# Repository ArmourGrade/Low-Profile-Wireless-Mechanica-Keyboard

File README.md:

# Low-Profile-Wireless-Mechanica-Keyboard
Wireless Mechanical Keyboard featuring the Nice Nano dev board

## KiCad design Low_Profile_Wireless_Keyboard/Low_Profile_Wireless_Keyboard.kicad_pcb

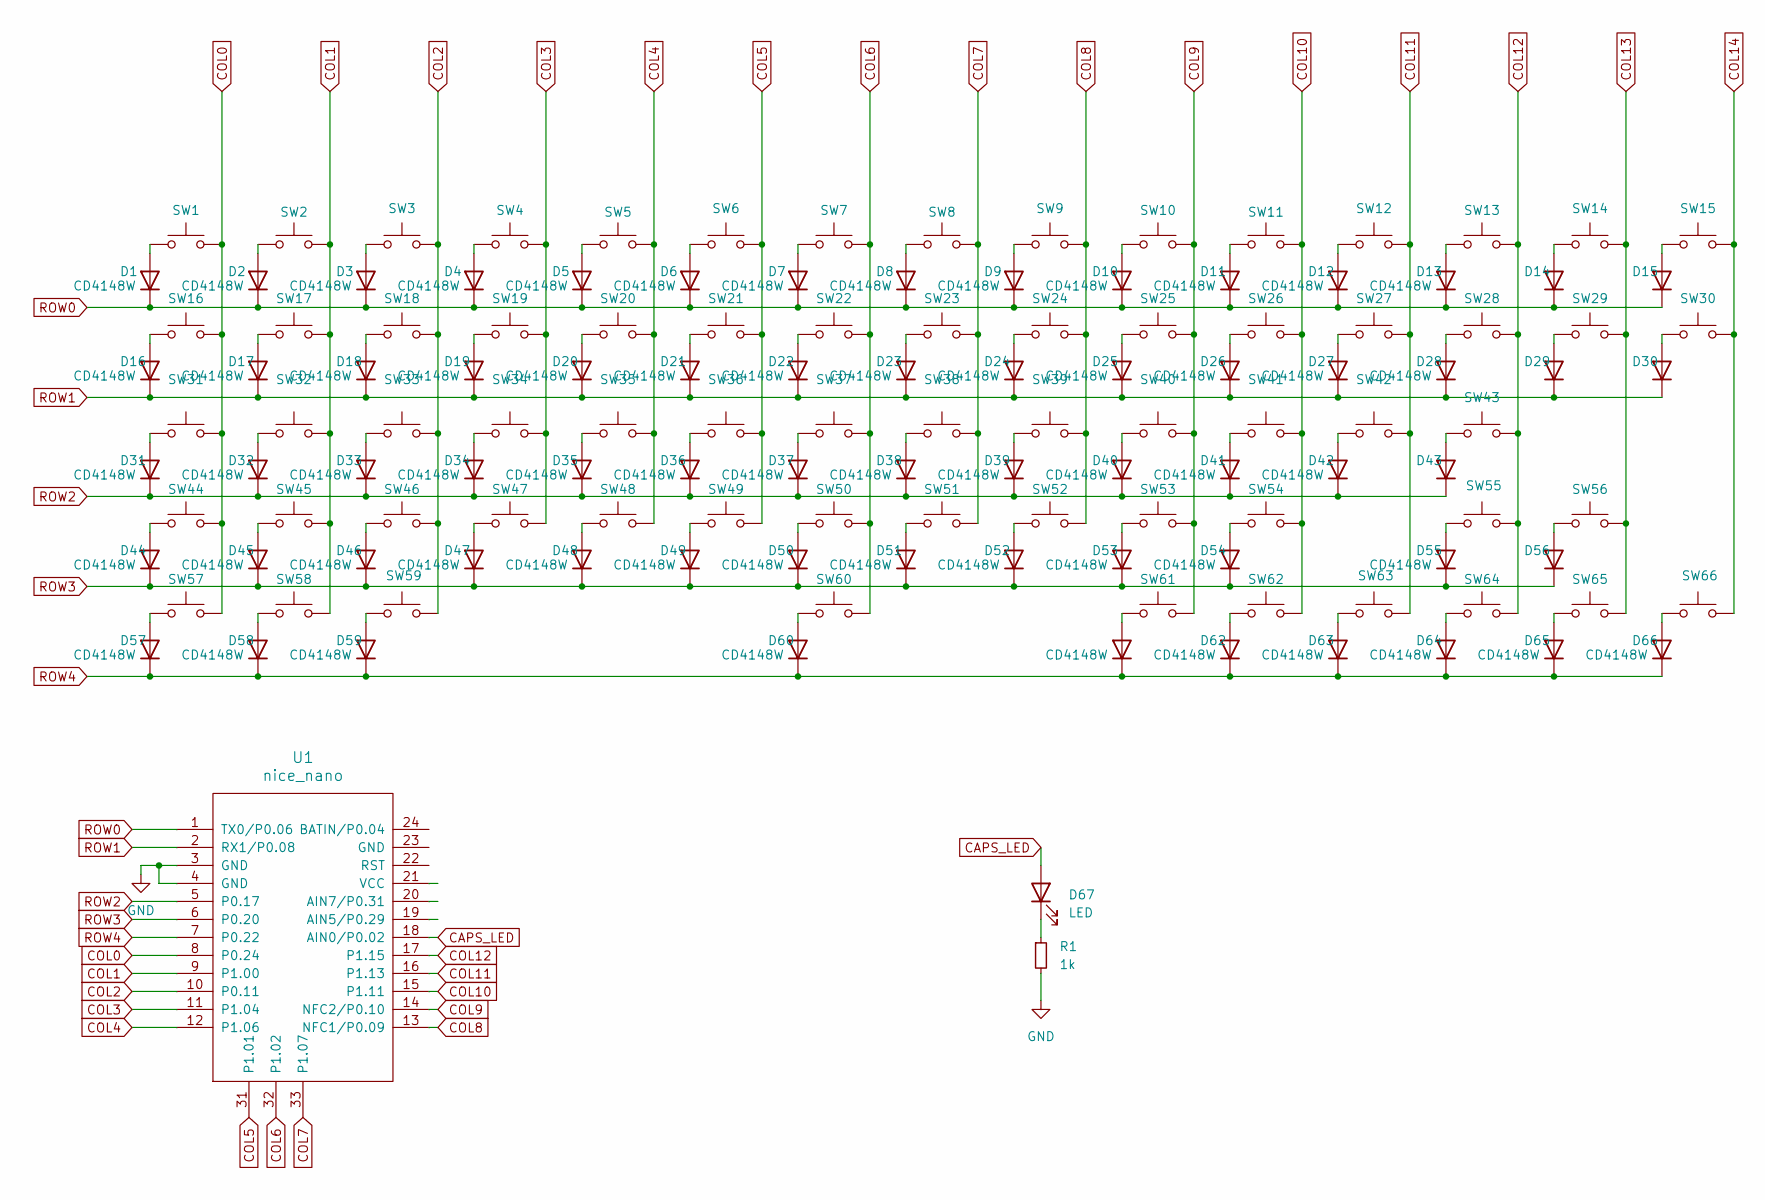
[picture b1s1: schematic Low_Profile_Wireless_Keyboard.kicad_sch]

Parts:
D1, D2, D3, D4, D5, D6, D7, D8, D9, D10, D11, D12, D13, D14, D15, D16, D17, D18, D19, D20, D21, D22, D23, D24, D25, D26, D27, D28, D29, D30, D31, D32, D33, D34, D35, D36, D37, D38, D39, D40, D41, D42, D43, D44, D45, D46, D47, D48, D49, D50, D51, D52, D53, D54, D55, D56, D57, D58, D59, D60, D61, D62, D63, D64, D65, D66: CD4148W; D_0805_2012Metric
D67: LED; LED_0603_1608Metric
R1: 1k; R_0805_2012Metric_Pad1.20x1.40mm_HandSolder
SW1, SW2, SW3, SW4, SW5, SW6, SW7, SW8, SW9, SW10, SW11, SW12, SW13, SW14, SW15, SW16, SW17, SW18, SW19, SW20, SW21, SW22, SW23, SW24, SW25, SW26, SW27, SW28, SW29, SW30, SW31, SW32, SW33, SW34, SW35, SW36, SW37, SW38, SW39, SW40, SW41, SW42, SW43, SW45, SW46, SW47, SW48, SW49, SW50, SW51, SW52, SW53, SW54, SW56, SW57, SW58, SW59, SW61, SW62, SW63, SW64, SW65, SW66: SW_Push; SW_Hotswap_Kailh_Choc_V1V2
SW44, SW55: SW_Push; SW_Hotswap_Kailh_Choc_V1V2_2.25u
SW60: SW_Push; SW_Hotswap_Kailh_Choc_V1V2_6.25u
U1: nice_nano

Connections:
CAPS_LED: D67.2 (A), U1.18 (AIN0/P0.02)
COL0: SW1.2, SW16.2, SW31.2, SW44.2, SW57.2, U1.8 (P0.24)
COL1: SW2.2, SW17.2, SW32.2, SW45.2, SW58.2, U1.9 (P1.00)
COL2: SW3.2, SW18.2, SW33.2, SW46.2, SW59.2, U1.10 (P0.11)
COL3: SW4.2, SW19.2, SW34.2, SW47.2, U1.11 (P1.04)
COL4: SW5.2, SW20.2, SW35.2, SW48.2, U1.12 (P1.06)
COL5: SW6.2, SW21.2, SW36.2, SW49.2, U1.31 (P1.01)
COL6: SW7.2, SW22.2, SW37.2, SW50.2, SW60.2, U1.32 (P1.02)
COL7: SW8.2, SW23.2, SW38.2, SW51.2, U1.33 (P1.07)
COL8: SW9.2, SW24.2, SW39.2, SW52.2, U1.13 (NFC1/P0.09)
COL9: SW10.2, SW25.2, SW40.2, SW53.2, SW61.2, U1.14 (NFC2/P0.10)
COL10: SW11.2, SW26.2, SW41.2, SW54.2, SW62.2, U1.15 (P1.11)
COL11: SW12.2, SW27.2, SW42.2, SW63.2, U1.16 (P1.13)
COL12: SW13.2, SW28.2, SW43.2, SW55.2, SW64.2, U1.17 (P1.15)
COL13: SW14.2, SW29.2, SW56.2, SW65.2
COL14: SW15.2, SW30.2, SW66.2
GND: R1.2, U1.3 (GND), U1.4 (GND)
unnamed: D1.2 (A), SW1.1
unnamed: D2.2 (A), SW2.1
unnamed: D3.2 (A), SW3.1
unnamed: D4.2 (A), SW4.1
unnamed: D5.2 (A), SW5.1
unnamed: D6.2 (A), SW6.1
unnamed: D7.2 (A), SW7.1
unnamed: D8.2 (A), SW8.1
unnamed: D9.2 (A), SW9.1
unnamed: D10.2 (A), SW10.1
unnamed: D11.2 (A), SW11.1
unnamed: D12.2 (A), SW12.1
unnamed: D13.2 (A), SW13.1
unnamed: D14.2 (A), SW14.1
unnamed: D15.2 (A), SW15.1
unnamed: D16.2 (A), SW16.1
unnamed: D17.2 (A), SW17.1
unnamed: D18.2 (A), SW18.1
unnamed: D19.2 (A), SW19.1
unnamed: D20.2 (A), SW20.1
unnamed: D21.2 (A), SW21.1
unnamed: D22.2 (A), SW22.1
unnamed: D23.2 (A), SW23.1
unnamed: D24.2 (A), SW24.1
unnamed: D25.2 (A), SW25.1
unnamed: D26.2 (A), SW26.1
unnamed: D27.2 (A), SW27.1
unnamed: D28.2 (A), SW28.1
unnamed: D29.2 (A), SW29.1
unnamed: D30.2 (A), SW30.1
unnamed: D31.2 (A), SW31.1
unnamed: D32.2 (A), SW32.1
unnamed: D33.2 (A), SW33.1
unnamed: D34.2 (A), SW34.1
unnamed: D35.2 (A), SW35.1
unnamed: D36.2 (A), SW36.1
unnamed: D37.2 (A), SW37.1
unnamed: D38.2 (A), SW38.1
unnamed: D39.2 (A), SW39.1
unnamed: D40.2 (A), SW40.1
unnamed: D41.2 (A), SW41.1
unnamed: D42.2 (A), SW42.1
unnamed: D43.2 (A), SW43.1
unnamed: D44.2 (A), SW44.1
unnamed: D45.2 (A), SW45.1
unnamed: D46.2 (A), SW46.1
unnamed: D47.2 (A), SW47.1
unnamed: D48.2 (A), SW48.1
unnamed: D49.2 (A), SW49.1
unnamed: D50.2 (A), SW50.1
unnamed: D51.2 (A), SW51.1
unnamed: D52.2 (A), SW52.1
unnamed: D53.2 (A), SW53.1
unnamed: D54.2 (A), SW54.1
unnamed: D55.2 (A), SW55.1
unnamed: D56.2 (A), SW56.1
unnamed: D57.2 (A), SW57.1
unnamed: D58.2 (A), SW58.1
unnamed: D59.2 (A), SW59.1
unnamed: D60.2 (A), SW60.1
unnamed: D61.2 (A), SW61.1
unnamed: D62.2 (A), SW62.1
unnamed: D63.2 (A), SW63.1
unnamed: D64.2 (A), SW64.1
unnamed: D65.2 (A), SW65.1
unnamed: D66.2 (A), SW66.1
unnamed: D67.1 (K), R1.1
ROW0: D1.1 (K), D2.1 (K), D3.1 (K), D4.1 (K), D5.1 (K), D6.1 (K), D7.1 (K), D8.1 (K), D9.1 (K), D10.1 (K), D11.1 (K), D12.1 (K), D13.1 (K), D14.1 (K), D15.1 (K), U1.1 (TX0/P0.06)
ROW1: D16.1 (K), D17.1 (K), D18.1 (K), D19.1 (K), D20.1 (K), D21.1 (K), D22.1 (K), D23.1 (K), D24.1 (K), D25.1 (K), D26.1 (K), D27.1 (K), D28.1 (K), D29.1 (K), D30.1 (K), U1.2 (RX1/P0.08)
ROW2: D31.1 (K), D32.1 (K), D33.1 (K), D34.1 (K), D35.1 (K), D36.1 (K), D37.1 (K), D38.1 (K), D39.1 (K), D40.1 (K), D41.1 (K), D42.1 (K), D43.1 (K), U1.5 (P0.17)
ROW3: D44.1 (K), D45.1 (K), D46.1 (K), D47.1 (K), D48.1 (K), D49.1 (K), D50.1 (K), D51.1 (K), D52.1 (K), D53.1 (K), D54.1 (K), D55.1 (K), D56.1 (K), U1.6 (P0.20)
ROW4: D57.1 (K), D58.1 (K), D59.1 (K), D60.1 (K), D61.1 (K), D62.1 (K), D63.1 (K), D64.1 (K), D65.1 (K), D66.1 (K), U1.7 (P0.22)

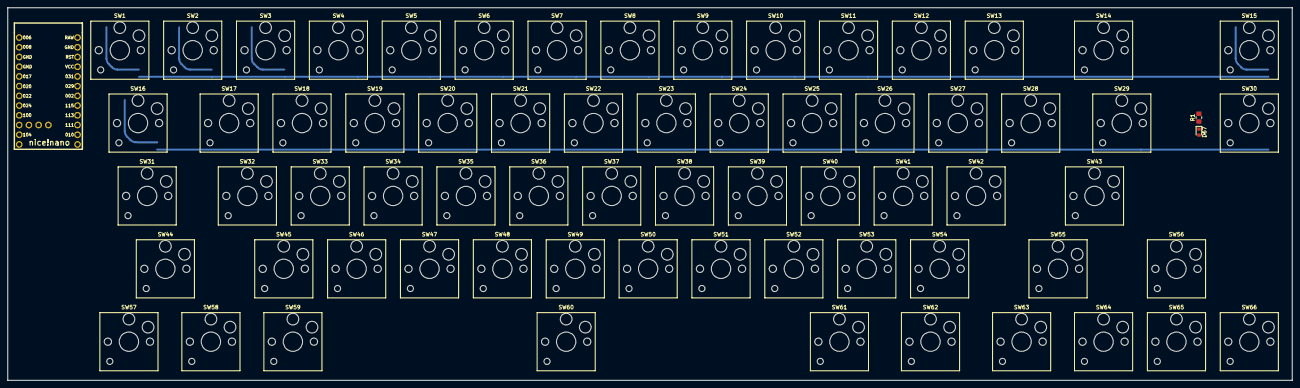
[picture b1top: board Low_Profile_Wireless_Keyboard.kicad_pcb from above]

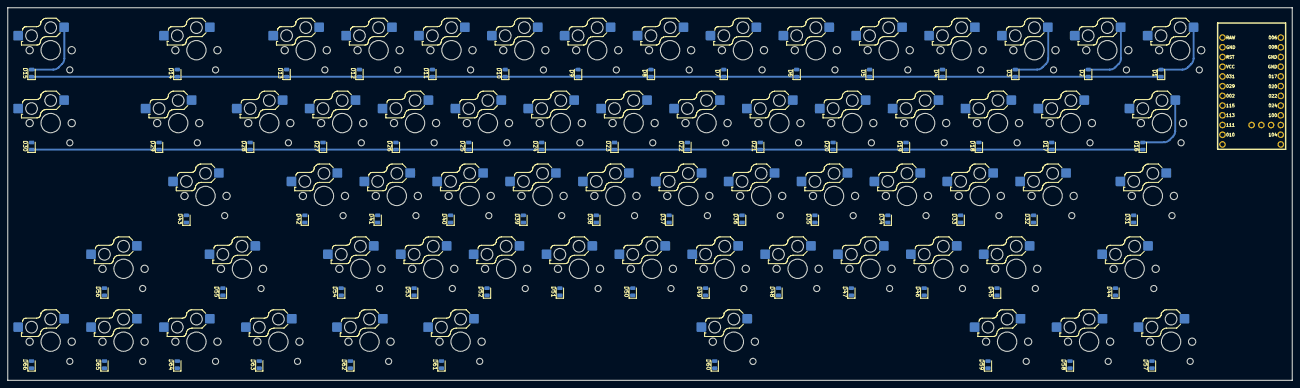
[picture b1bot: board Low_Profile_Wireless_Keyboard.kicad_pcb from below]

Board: 2 copper layers, 335.8 x 97.4 mm, 135 parts (66 on the bottom side), 89 nets.

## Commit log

2024-12-14 Added basic unfinished KiCAD files
